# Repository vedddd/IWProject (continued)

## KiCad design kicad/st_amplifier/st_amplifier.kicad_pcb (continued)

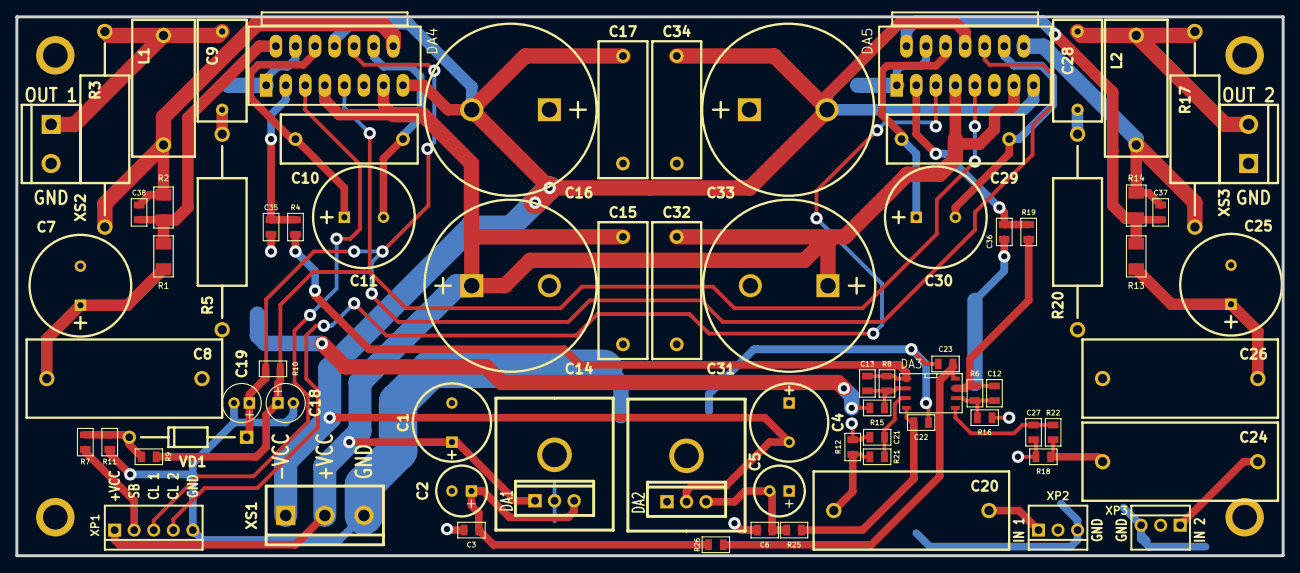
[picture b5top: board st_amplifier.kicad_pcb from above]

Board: 2 copper layers, 164.5 x 70.0 mm, 82 parts (0 on the bottom side), 39 nets.

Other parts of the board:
1_PIN, 1_PIN#2, 1_PIN#3, 1_PIN#4, 1_PIN#5, 1_PIN#6: P***; 1_pin

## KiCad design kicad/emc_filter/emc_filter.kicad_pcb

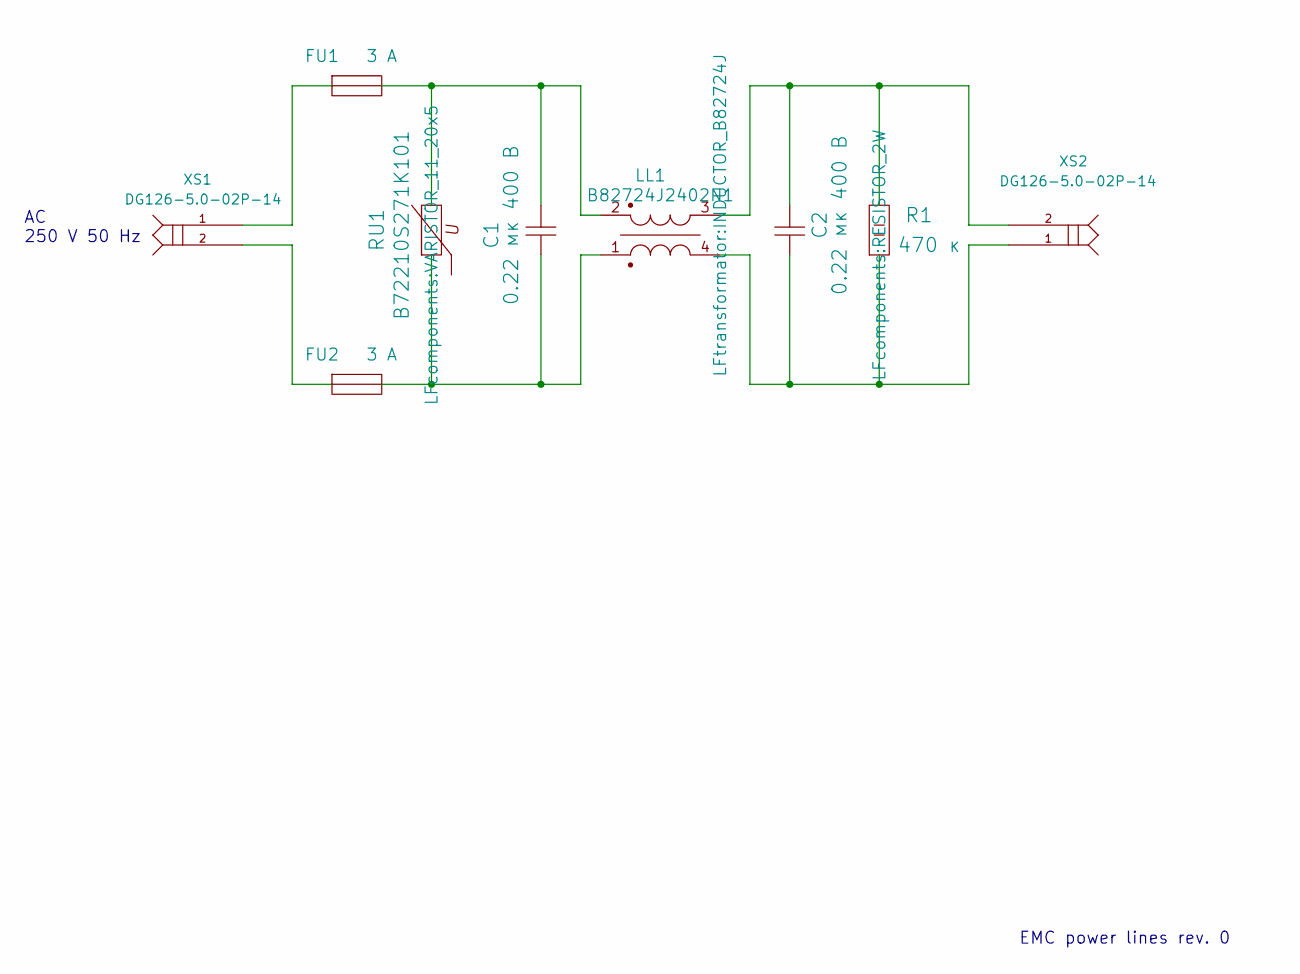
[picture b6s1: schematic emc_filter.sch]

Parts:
C1, C2: 0.22 мк 400 В; CAPACITOR_15_18x7
FU1, FU2: 3 A; FU_PTF15B
LL1: B82724J2402N1; INDUCTOR_B82724J
R1: 470 к; RESISTOR_2W
RU1: B72210S271K101; VARISTOR_11_20x5
XS1, XS2: DG126-5.0-02P-14; DG126-5.0-02P-14~

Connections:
unnamed: C1.1, FU2.2, LL1.1, RU1.1
unnamed: C1.2, FU1.2, LL1.2, RU1.2
unnamed: C2.1, LL1.4, R1.1, XS2.1
unnamed: C2.2, LL1.3, R1.2, XS2.2
unnamed: FU1.1, XS1.1
unnamed: FU2.1, XS1.2

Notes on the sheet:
AC 250 V 50 Hz
EMC power lines rev. 0

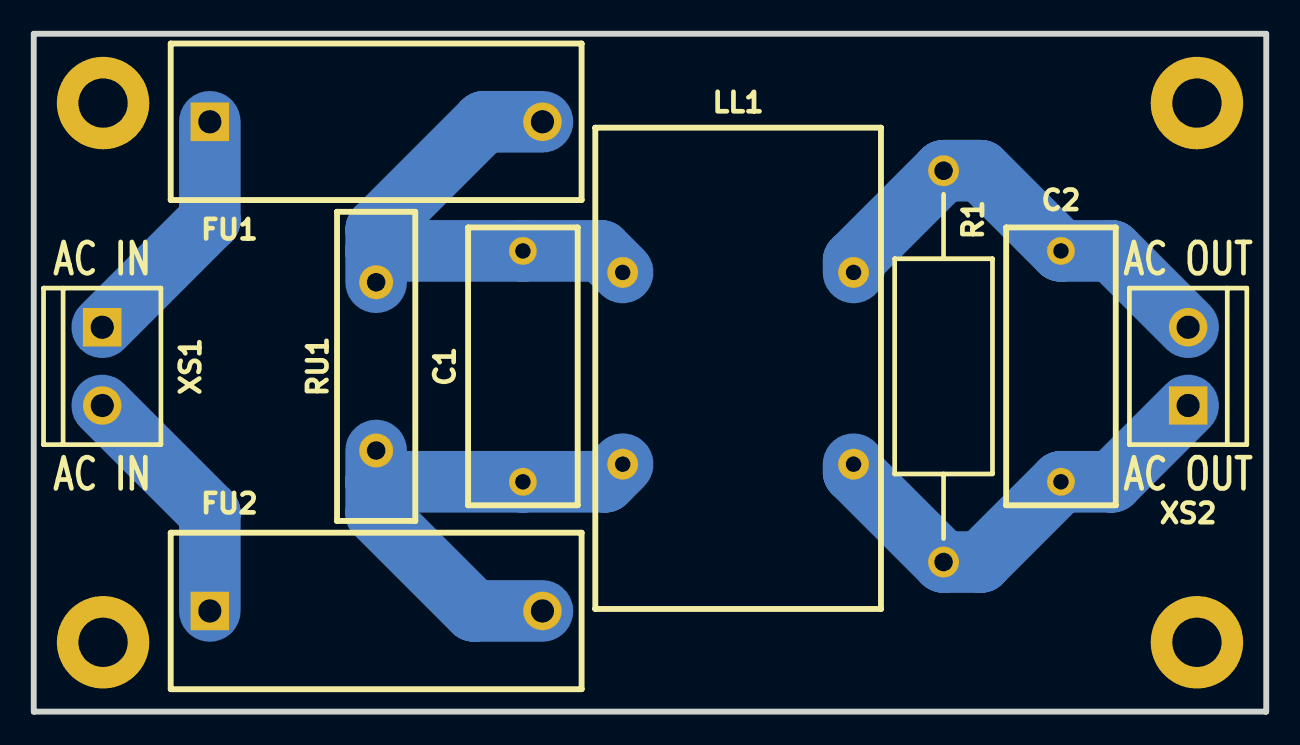
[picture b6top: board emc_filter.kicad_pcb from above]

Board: 2 copper layers, 80.0 x 44.0 mm, 13 parts (0 on the bottom side), 6 nets.

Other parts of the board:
1_PIN, 1_PIN#2, 1_PIN#3, 1_PIN#4: P***; 1_pin

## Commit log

2015-04-12 first commmit
2015-04-12 Adding stereo amplifier on TDA7293.
2015-04-15 New commit.
2015-04-30 Adding board st_amplifier.
2015-05-03 Adding mc power supply.
2015-05-07 Completely threw PCB board st_amplifier.
2015-05-22 Fixed errors.
2015-05-27 He completed the first version of the board st_amplifier.
2015-05-28 Adding new version st_amplifier.
2015-06-07 Add emc filter.
2015-06-14 Add new mc_amplifier.
2015-06-14 Add 2 way active filter.
2015-06-25 Adding new shema for 2 way active filter.
2015-06-30 Adding new version st_amplifier (rev. 1).
2015-07-19 2-way active filter.
2015-09-12 Add new version 2-way active filter.
2015-09-13 Send to production of 2-way active filter.
2015-11-01 Add board ver_0.
2015-11-22 Corrected power amplifier circuit (st_amplifier).
2015-12-14 Moved to kicad 4.0.0
2016-01-18 Add description to the schemes.
2016-05-27 Adding power supply +/-100V, 10A.
2016-06-19 Развёл плату стабилизатора на +/-100В 15А.
2016-06-22 Подготовил плату PS10015 к отправке на изготовление.
2016-10-29 Добавил схему усилителя по мотивам Mark II.
2016-10-29 Улучшил входной диф. каскад у Mark III.
2016-10-30 Поправил схему усилителя Mark III.
2017-02-12 Добавил провенную схему таймера на NE555.
2017-02-12 Поправил схему таймера на NE555.
2017-03-07 Добавил в схему с реле времени на NE555 логику при срабатывание при не нулевом сопротивление контактов датчика.
2018-03-18 Поправил схему источника питания для микрофонного усилителя.
2018-03-29 Поравил схему источника питания микрофона.
2019-11-25 Добавил новую версию усилителя mc_amplifier_rev_1.
2019-11-26 Порпвил схему и отравил плату mc_amplifier rev1 на изготовление.
2019-11-26 Поправил схему и отравил плату mc_amplifier rev1 на изготовление.
2019-11-26 Поправил полигон на плате и отравил плату mc_amplifier rev1 на изготовление.
2020-01-12 Добавил новую ревизию схемы mc_amplifier (rev_2).
2020-01-14 Проверил работоспособность платы mc_amplifier ver_1.
2020-04-05 Добавил схему источника питания на 48В.
2020-10-05 Добавил новую версию микрофонного источника питания.
2020-10-17 Поправил st_amplifier для новой версии kicad.
2021-01-27 Приступил к разработке блока питания ver.3 для измерительного микрофофона.
2021-01-28 Приступил к расположению компонентов на плате mc_power_supply_ver3.
2021-01-28 Закончил предварительную трассировку плат MM power supply ver. 3.0.
2021-02-02 Заменил трансформатор на плате MM power supply ver. 3.0. и приступил к повторной трассировке.
2021-02-02 Повторно произвёл трассировку платы mc_power_supply_ver_3.0.
2021-02-02 Поправил трассировку на платы mc_power_supply_ver_3.0.
2021-02-05 Поравил плату mc_power_supply ver.3.
2021-02-11 Поправлил схему фильтров active_low-pass_filter.
2021-02-12 Продолжил разрабатывать плату mc_power_supply.
2021-02-12 Отправил печатную плату mc_power_supply в производство.
2021-02-16 Повторно отправил плату mm_power_supply_v3 в производство.
2021-02-19 Добавил проект микрофонного усилителя с переключаемым коэффициентом усиления adjustable_mm_amplifier.
2021-02-20 Закончил разрабатывать схему усилителя для микрофонов.
2021-02-23 Продолжил разрабатывать плату микрофонного услителя на +9...+48.
2021-02-26 Добавил конденсаторы в повторитель сабвуферного фильтра для удаления самопроизвольного возмбуждения каскада.
2021-03-05 Успешно изготовил и проверил первый экземляр платы MM_power_supply_ver. 3.0
2021-03-11 Продолжил разрабатывать adjustable_mm_amplifier.
